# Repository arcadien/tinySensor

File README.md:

# TinySensor 

TinySensor aims to provide a customisable firmware and a hardware design for low-power environment sensors using wireless communication.

In the complete system, data is processed by a [Domoticz](https://domoticz.com/)/[RFlink](http://www.rflink.nl/blog2/) couple.
Data decoding is also tested using [RTL_433](https://github.com/merbanan/rtl_433) decoder.
Large part of the code, especially wireless encoders, are unit-tested.

## Supported MCUs
* ATTiny84a
* ATMega328p: started on branch `feat/328p_hal`, not merged

## Supported sensors
* I2C sensors (eg. [Bosch BME/BMP280](https://www.bosch-sensortec.com/bst/products/all_products/bme280))
* Analog sensors (eg. [LM35](http://www.ti.com/lit/ds/symlink/lm35.pdf))
* OneWire sensors (eg. [Dallas DS18S20](https://datasheets.maximintegrated.com/en/ds/DS18S20.pdf))
* Luminosity sensor ([ROHM BH1750](https://www.mouser.com/datasheet/2/348/bh1750fvi-e-186247.pdf), I2C)

## Wireless technology
* "one pin" emitters. Tested with low-cost 433 MHz emitters.

## Wireless protocols
* Environment frame (temperature, humidity, pressure): Oregon Scientific v3 **or** Lacrosse WS7000, at most one per build. A build without either sends no environment frame.
* Luminosity: always a dedicated Lacrosse WS7000 frame (Oregon has no light frame), so `LACROSSE_ID` is required whenever the BH1750 is fitted.
* Battery level and analog input: optional X10 RFXmeter frames, not sent when the battery is low.

## Used libraries
Various libraries are used here, and some where tweaked to remove any Arduino dependencies, making the whole firmware more compact:
* Sparkfun [BME280 sensor library](https://github.com/sparkfun/SparkFun_BME280_Arduino_Library) with all SPI related code removed
* [Tiny I2C](https://github.com/arcadien/tiny-i2c.git) of [David Johnson-Davies](https://github.com/technoblogy)
* [Unity test harness](http://www.throwtheswitch.org/unity) from Throw The Switch, for all testing code
* DS18B20 library of [Jacek Wieczorek](https://github.com/Jacajack/avr-ds18b20)

## Useful documentation about low power AVR
* [AVR4013: picoPower Basics](http://www.microchip.com/downloads/en/AppNotes/doc8349.pdf)

## Development

The firmware is built with [PlatformIO](https://platformio.org/) and configured entirely at build time: each physical sensor is one PlatformIO environment (`S_02`…`S_05`, `robot`, `devmodule`, `SOLAR_TEST`) whose `build_flags` select protocol, sensors and calibration. See [docs/environments.md](docs/environments.md) to calibrate or add a board.

```bash
pio test -e native_debug        # encoder and library unit tests, on the host
pio test -e native_cycle_oregon # one measurement cycle (runCycle) per build variant;
                                # also native_cycle_oregon_vcc, _lacrosse, _x10
pio run -e S_02                 # firmware for one board
pio run -e S_02 -t upload       # flash it
```

CI runs the native tests, compile-fail checks for invalid flag combinations (`test/compile_fail/`), sensor-variant checks (`test/build_variants/`), `clang-format` and a build of every board.

* Architecture: [docs/architecture.md](docs/architecture.md)
* Step debugging over debugWIRE: [docs/debugging.md](docs/debugging.md)
* Requirements: `requirements/*.md` (requirement-based development, see `CLAUDE.md`)

## Hardware and enclosure

* KiCad board (v3.0) in `hardware/tinysensor/`, with its [backlog](hardware/tinysensor/BACKLOG.md) and a [rework guide for v2.2 boards](hardware/tinysensor/REWORK_v2.2.md).
* OpenSCAD enclosures (wall box, radiation shield, mushroom) in `openscad/`, see [openscad/README.md](openscad/README.md).

## Hardware options

TinySensor can use combination of sensors, the limit comes from amount of flash memory on the ATTiny.

### DS18B20

OneWire sensor, cheap and efficient.

### BMP/BME 280 environment sensor
The [BMP280](https://www.bosch-sensortec.com/products/environmental-sensors/pressure-sensors/pressure-sensors-bmp280-1.html) and the [BME280](https://www.bosch-sensortec.com/products/environmental-sensors/humidity-sensors-bme280/) share the same library, but the BME provide humidity sensing, and thus use more memory.

### Analog sensor

Analog sensor can be used for [LM35](https://www.ti.com/lit/ds/symlink/lm35.pdf) temperature sensor, or [LDR](https://en.wikipedia.org/wiki/Photoresistor).

### LM35 temperature sensor

On v2.2 and v3.0 boards running from 2×AA/AAA, the LM35 can be powered by an off-board 5 V boost module switched on PB2 only during measurements (`USE_SWITCHED_5V`), see [VARIANTE_LM35.md](hardware/tinysensor/VARIANTE_LM35.md). The instructions below are for v2.1.

#### Without negative temperature support
A 0v ground reference is needed.
Solder pads *2* and *3* of **J4**, (rear side) as well **JP3**. 

#### With negative temperature support
In the case of a *-CAZ* version, temperature below 0 can be measured. 
To allow this, two 1N914 diodes must be placed to put the sensor reference below 0v. This setup is documented in the LM35 datasheet.
On TinySensor board v2.1 and up, this can be implemented by:
* solding **D2** and **D3** diodes
* solding **R4** with a value of 18k
* solding **JP3** to bypass C3 capacitor
* solding pads *1* and *2* of **J4** (rear side) to set ground reference.

#### Notes about swing

You can add a filter capacitor *C3* to avoid swing if the wire is long. In this case, do not solder *JP3*.
See datasheet for details.

### LDR
Use the right value for **R4** (should match the used LDR) and solder **JP3** and, on **JP4**, middle and *3* pads. This way, there will be no RC filter (no cap because of **J3**) and Vss analog reference thanks of **JP4**.

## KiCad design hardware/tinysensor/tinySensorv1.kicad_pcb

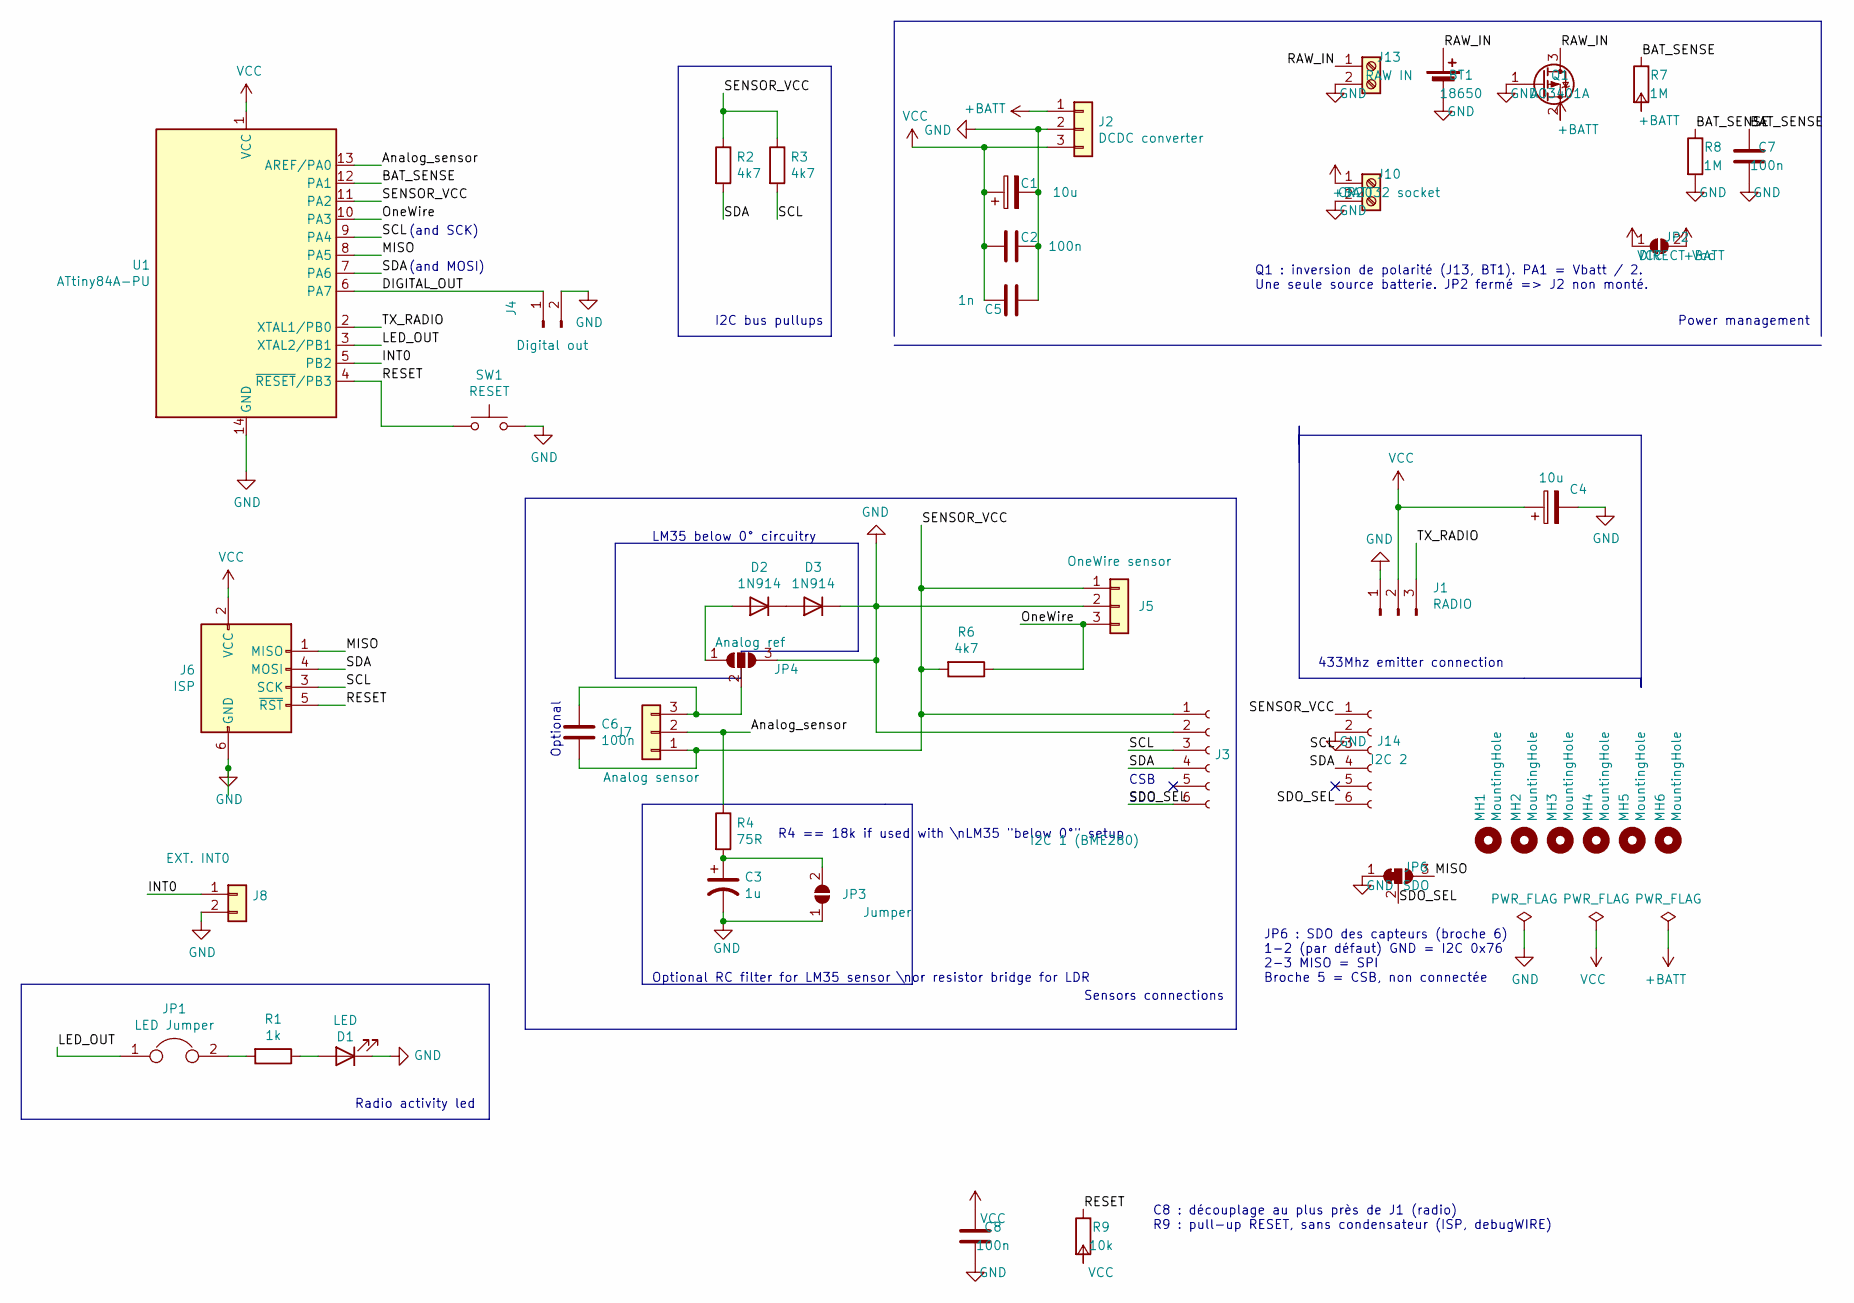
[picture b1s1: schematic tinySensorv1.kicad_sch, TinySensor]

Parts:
BT1: 18650; BatteryHolder_MPD_BH-18650-PC2
C1, C4: 10u; CP_Radial_D5.0mm_P2.50mm
C2: 100n; C_Rect_L7.0mm_W2.0mm_P5.00mm
C3: 1u; CP_Radial_D4.0mm_P1.50mm
C5: 1n; C_Disc_D3.0mm_W1.6mm_P2.50mm
C6, C7, C8: 100n; C_0805_2012Metric
D1: LED; LED_D1.8mm_W3.3mm_H2.4mm
D2, D3: 1N914; D_DO-35_SOD27_P7.62mm_Horizontal
J1: RADIO; PinHeader_1x03_P2.54mm_Vertical
J2: DCDC converter; DC-DC_0.9v-3.3v_to_3.3v
J3: I2C 1 (BME280); JST_EH_B6B-EH-A_1x06_P2.50mm_Vertical
J4: Digital out; PinHeader_1x02_P2.54mm_Vertical
J5: OneWire sensor; PinHeader_1x03_P2.54mm_Vertical
J6: ISP; ICSP_SOCKET_MINI_2x3
J7: Analog sensor; PinHeader_1x03_P2.54mm_Vertical
J8: EXT. INT0; PinHeader_1x02_P2.54mm_Vertical
J10: CR2032 socket; BatteryHolder_Keystone_106_1x21mm
J13: RAW IN; TerminalBlock_bornier-2_P5.08mm
J14: I2C 2; JST_EH_B6B-EH-A_1x06_P2.50mm_Vertical
JP1: LED Jumper; PinHeader_1x02_P2.54mm_Vertical
JP2: DIRECT Vcc; SolderJumper-2_P1.3mm_Open_TrianglePad1.0x1.5mm
JP3: Jumper; SolderJumper-2_P1.3mm_Open_TrianglePad1.0x1.5mm
JP4: Analog ref; SolderJumper-3_P1.3mm_Open_Pad1.0x1.5mm_NumberLabels
JP6: SDO; SolderJumper-3_P1.3mm_Bridged12_RoundedPad1.0x1.5mm
MH1, MH2, MH3, MH4, MH5, MH6: MountingHole; MountingHole_2.7mm_M2.5
Q1: AO3401A; SOT-23
R1: 1k; R_Axial_DIN0204_L3.6mm_D1.6mm_P7.62mm_Horizontal
R2, R3, R6: 4k7; R_Axial_DIN0204_L3.6mm_D1.6mm_P7.62mm_Horizontal
R4: 75R; R_Axial_DIN0204_L3.6mm_D1.6mm_P7.62mm_Horizontal
R7, R8: 1M; R_0805_2012Metric
R9: 10k; R_0805_2012Metric
SW1: RESET; SW_PUSH_6mm_H4.3mm
U1: ATtiny84A-PU; DIP-14_W7.62mm

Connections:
+BATT: J2.1, J10.1, JP2.2 (B), Q1.2 (S), R7.2
/Analog_sensor: J7.2, R4.1, U1.13 (AREF/PA0)
/BAT_SENSE: C7.1, R7.1, R8.1, U1.12 (PA1)
/DIGITAL_OUT: J4.1, U1.6 (PA7)
/INT0: J8.1, U1.5 (PB2)
/LED_OUT: JP1.1, U1.3 (XTAL2/PB1)
/MISO: J6.1 (MISO), JP6.3 (B), U1.8 (PA5)
/OneWire: J5.3, R6.1, U1.10 (PA3)
/RAW_IN: BT1.1 (+), J13.1, Q1.3 (D)
/RESET: J6.5 (~RST), R9.1, SW1.1, U1.4 (~RESET/PB3)
/SCL: J3.3, J6.3 (SCK), J14.3, R3.2, U1.9 (PA4)
/SDA: J3.4, J6.4 (MOSI), J14.4, R2.2, U1.7 (PA6)
/SDO_SEL: J3.6, J14.6, JP6.2 (C)
/SENSOR_VCC: C6.1, J3.1, J5.1, J7.1, J14.1, R2.1, R3.1, R6.2, U1.11 (PA2)
/TX_RADIO: J1.3, U1.2 (XTAL1/PB0)
GND: BT1.2 (-), C1.2, C2.1, C3.2, C4.2, C5.2, C7.2, C8.2, D1.1 (K), D3.1 (K), J1.1, J2.2, J3.2, J4.2, J5.2, J6.6 (GND), J8.2, J10.2, J13.2, J14.2, JP3.1 (A), JP4.3 (B), JP6.1 (A), Q1.1 (G), R8.2, SW1.2, U1.14 (GND)
unnamed: D1.2 (A), R1.1
unnamed: D2.2 (A), JP4.1 (A)
unnamed: D2.1 (K), D3.2 (A)
unnamed: C6.2, J7.3, JP4.2 (C)
unnamed: JP1.2, R1.2
unnamed: C3.1, JP3.2 (B), R4.2
VCC: C1.1, C2.2, C4.1, C5.1, C8.1, J1.2, J2.3, J6.2 (VCC), JP2.1 (A), R9.2, U1.1 (VCC)

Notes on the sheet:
CSB
Radio activity led
Power management
Optional RC filter for LM35 sensor \nor resistor bridge for LDR
(and SCK)
SDO
Sensors connections
LM35 below 0° circuitry
I2C bus pullups
(and MOSI)
Optional
R4 == 18k if used with \nLM35 "below 0°" setup
433Mhz emitter connection
Q1 : inversion de polarité (J13, BT1). PA1 = Vbatt / 2. Une seule source batterie. JP2 fermé => J2 non monté.
JP6 : SDO des capteurs (broche 6) 1-2 (par défaut) GND = I2C 0x76 2-3 MISO = SPI Broche 5 = CSB, non connectée
C8 : découplage au plus près de J1 (radio) R9 : pull-up RESET, sans condensateur (ISP, debugWIRE)

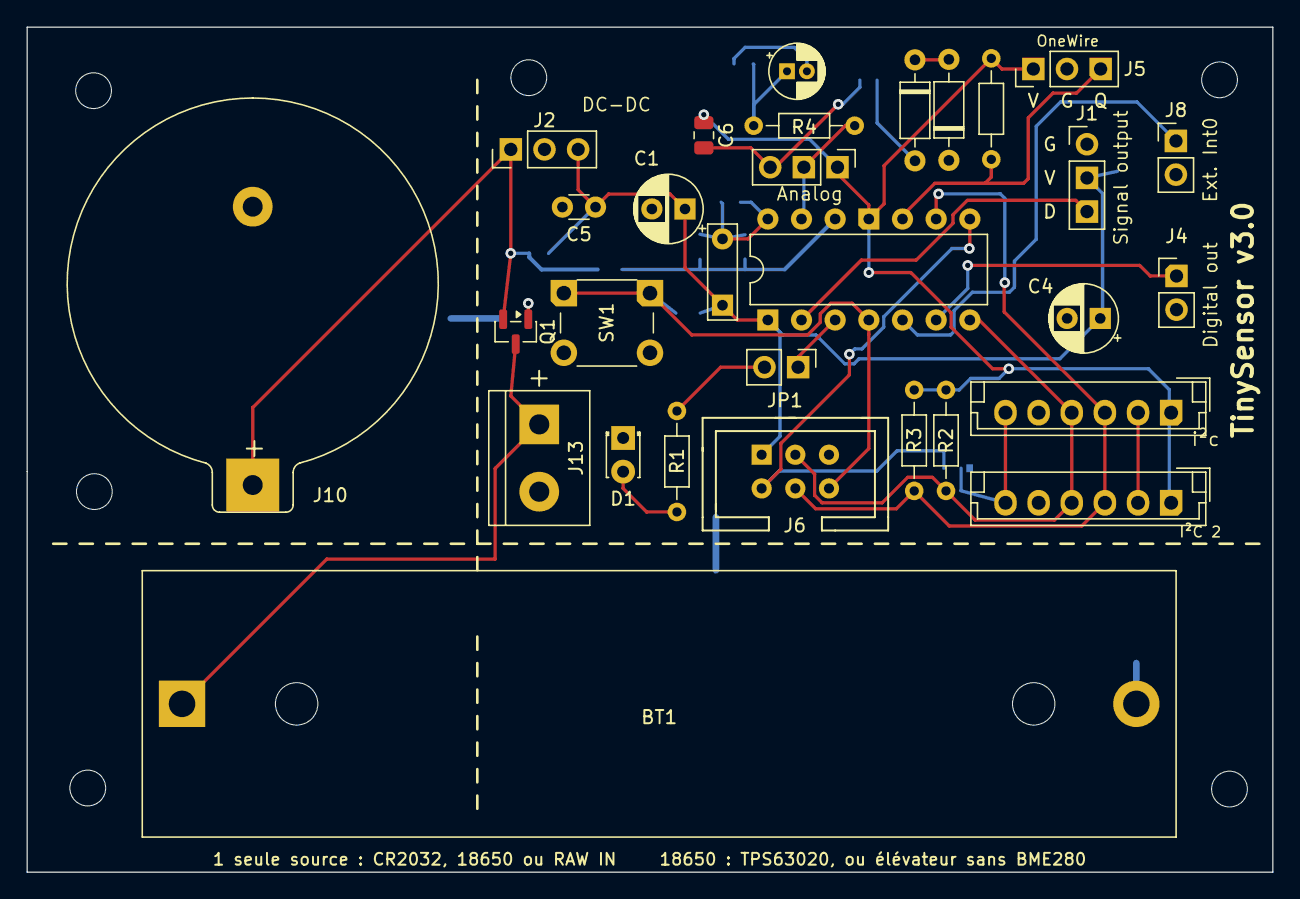
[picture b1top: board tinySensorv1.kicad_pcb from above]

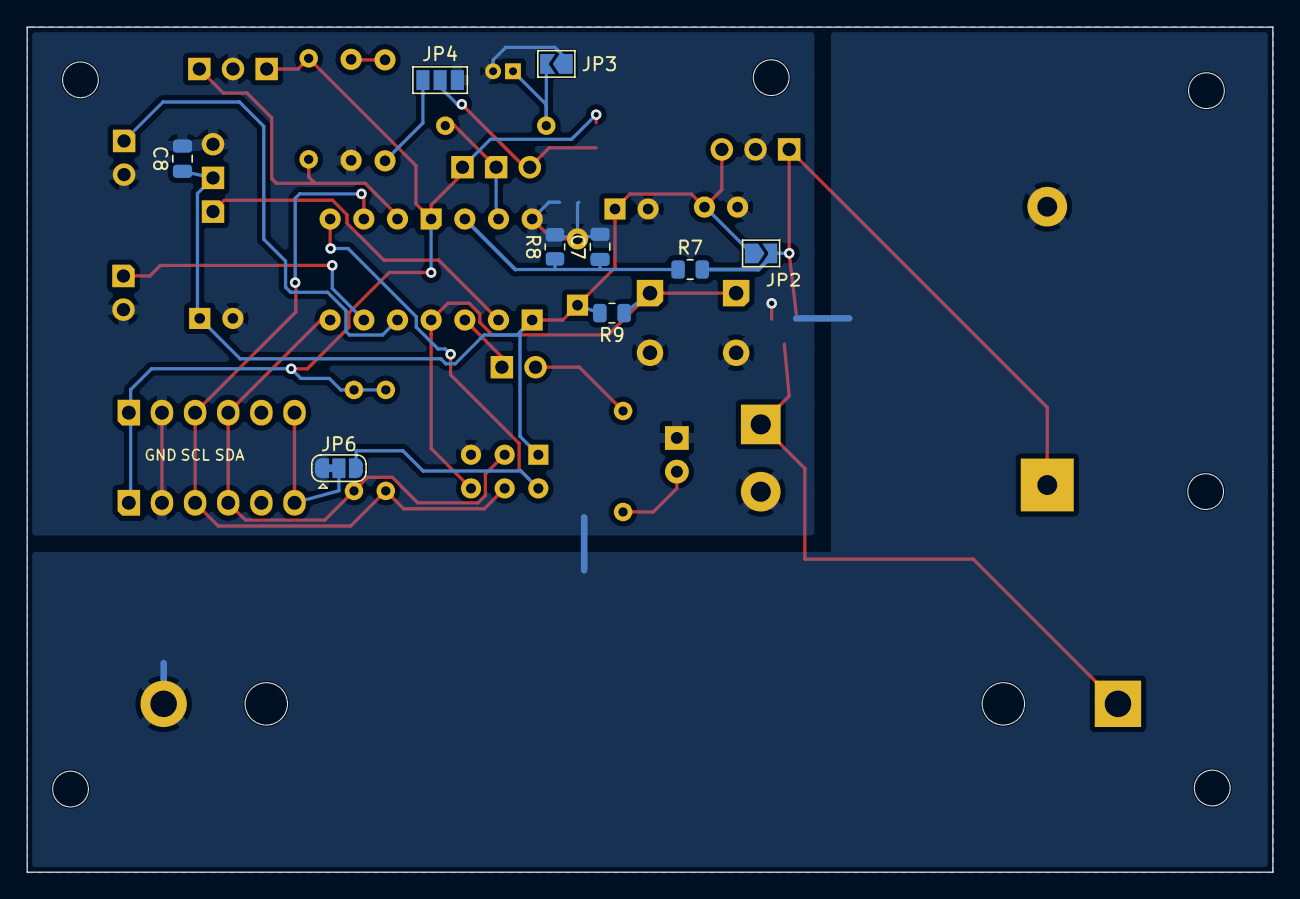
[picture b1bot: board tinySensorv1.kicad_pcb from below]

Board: 2 copper layers, 94.0 x 63.8 mm, 45 parts (9 on the bottom side), 23 nets.

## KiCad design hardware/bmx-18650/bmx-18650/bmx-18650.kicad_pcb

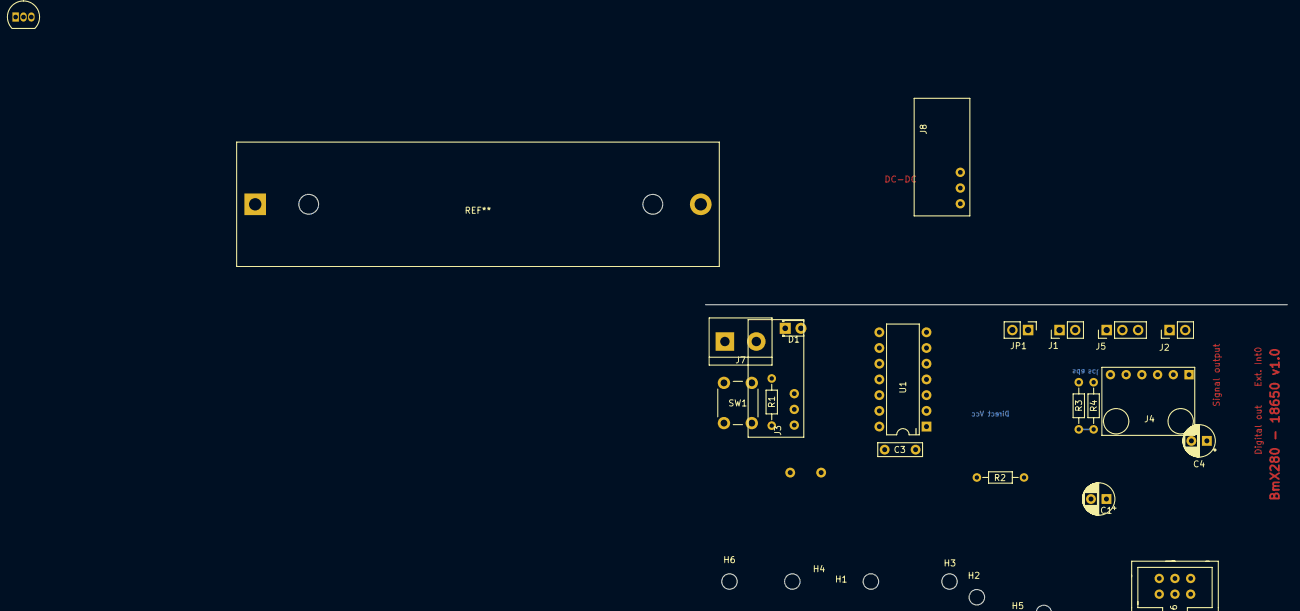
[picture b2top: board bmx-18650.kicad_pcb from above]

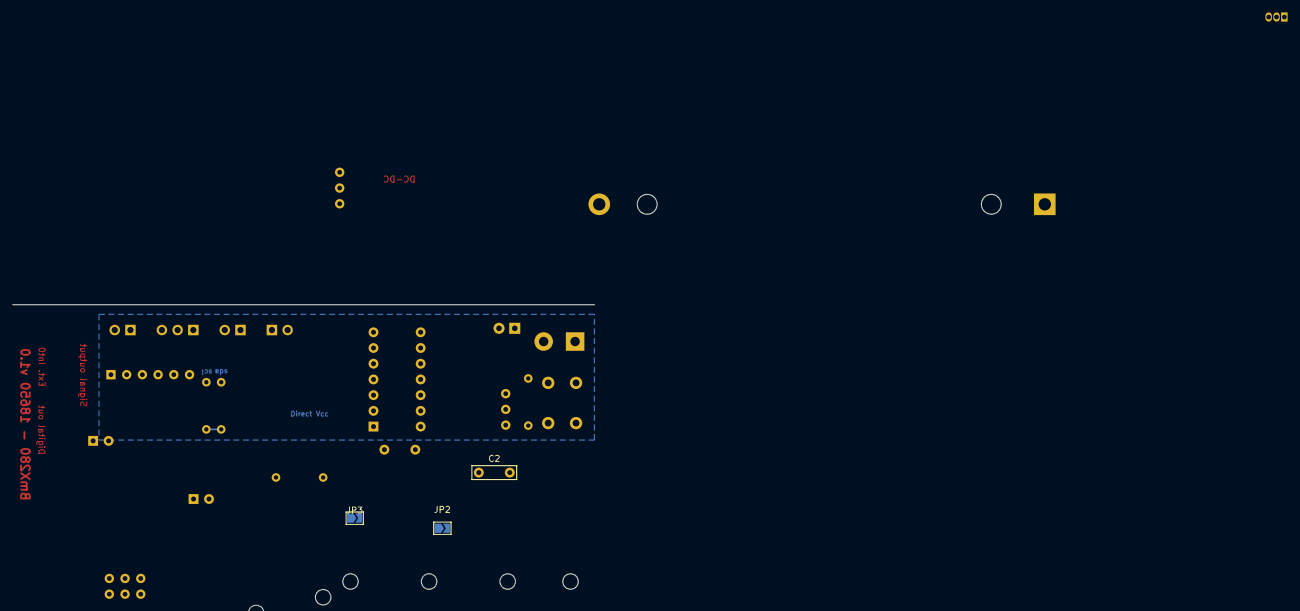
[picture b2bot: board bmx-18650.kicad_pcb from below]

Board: 2 copper layers, 29 parts (3 on the bottom side), 17 nets.

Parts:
C1, C4: 10u; CP_Radial_D5.0mm_P2.50mm
C2, C3: 100n; C_Rect_L7.0mm_W2.0mm_P5.00mm
D1: LED; LED_D1.8mm_W3.3mm_H2.4mm
H1, H2, H3, H4, H5, H6: MountingHole; MountingHole_2.5mm
J1: Ext. interrupt; PinHeader_1x02_P2.54mm_Vertical
J2: Digital out; PinHeader_1x02_P2.54mm_Vertical
J3: VCC charge pump; DC-DC_0.9v-3.3v_to_3.3v
J4: BMx280 socket; BMx280_breakout
J5: Radio emitter; PinHeader_1x03_P2.54mm_Vertical
J6: ISP; ICSP_SOCKET_MINI_2x3
J7: Terminal; TerminalBlock_bornier-2_P5.08mm
J8: RF charge pump; DC-DC_0.9v-3.3v_to_3.3v
JP1: LED Jumper; PinHeader_1x02_P2.54mm_Vertical
JP2, JP3: Bypass; SolderJumper-2_P1.3mm_Open_TrianglePad1.0x1.5mm
Q1: BS170; TO-92_Inline
R1, R3, R4: R; R_Axial_DIN0204_L3.6mm_D1.6mm_P7.62mm_Horizontal
R2: 10k; R_Axial_DIN0204_L3.6mm_D1.6mm_P7.62mm_Horizontal
SW1: SW_Push; SW_PUSH_6mm_H4.3mm
U1: ATtiny84A-PU; DIP-14_W7.62mm

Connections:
+BATT: J3.1, J7.1, J8.3, JP2.2 (B), JP3.1 (A), U1.12 (PA1)
/DIGITAL_OUT: J2.1, U1.6 (PA7)
/INT0: J1.1, U1.5 (PB2)
/LED_OUT: JP1.1, U1.3 (XTAL2/PB1)
/MISO: J6.1 (MISO), U1.8 (PA5)
/RESET: J6.5 (~RST), R2.1, SW1.1, U1.4 (~RESET/PB3)
/SCL: J4.3, J6.3 (SCK), R4.2, U1.9 (PA4)
/SDA: J4.4, J6.4 (MOSI), R3.2, U1.7 (PA6)
/SENSOR_VCC: J4.1, Q1.2 (G), R3.1, R4.1, U1.11 (PA2)
/TX_RADIO: J5.3, U1.2 (XTAL1/PB0)
GND: C1.2, C2.2, C3.1, C4.2, D1.2 (A), J1.2, J2.2, J3.2, J4.2, J4.6, J5.1, J6.6 (GND), J7.2, Q1.3 (S), SW1.2, U1.14 (GND)
unnamed: D1.1 (K), R1.1
unnamed: J8.2, Q1.1 (D)
unnamed: JP1.2, R1.2
unnamed: C2.1, U1.13 (AREF/PA0)
VCC: C1.1, C3.2, J3.3, J6.2 (VCC), JP2.1 (A), R2.2, U1.1 (VCC)
VDD: C4.1, J5.2, J8.1, JP3.2 (B)

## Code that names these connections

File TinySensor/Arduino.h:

/*
  pins_arduino.h - Pin definition functions for Arduino
  Part of Arduino - http://www.arduino.cc/

  Copyright (c) 2007 David A. Mellis
  Copyright (c) 2015~2020 Spence Konde

  This library is free software; you can redistribute it and/or
  modify it under the terms of the GNU Lesser General Public
  License as published by the Free Software Foundation; either
  version 2.1 of the License, or (at your option) any later version.

  This library is distributed in the hope that it will be useful,
  but WITHOUT ANY WARRANTY; without even the implied warranty of
  MERCHANTABILITY or FITNESS FOR A PARTICULAR PURPOSE.  See the GNU
  Lesser General Public License for more details.

  You should have received a copy of the GNU Lesser General
  Public License along with this library; if not, write to the
  Free Software Foundation, Inc., 59 Temple Place, Suite 330,
  Boston, MA  02111-1307  USA

  $Id: wiring.h 249 2007-02-03 16:52:51Z mellis $
*/

#ifndef Pins_Arduino_h
#define Pins_Arduino_h

#define ATTINYX4 1
#define __AVR_ATtinyX4__
#define USE_SOFTWARE_SPI 1

#include <avr/pgmspace.h>

#define NUM_DIGITAL_PINS            12
#define NUM_ANALOG_INPUTS           8

#define analogInputToDigitalPin(p)  (p)

#define digitalPinHasPWM(p)         ((p) == 5 || (p) == 6 || (p) == 7 || (p) == 8)

//This part has a USI, not an SPI module. Accordingly, there is no MISO/MOSI in hardware. There's a DI and a DO. When the chip is used as master, DI is used as MISO, DO is MOSI; the defines here specify the pins for master mode, as SPI master is much more commonly used in Arduino-land than SPI slave, and these defines are required for compatibility. Be aware of this when using the USI SPI fucntionality (and also, be aware that the MISO and MOSI markings on the pinout diagram in the datasheet are for ISP programming, where the chip is a slave. The pinout diagram included with this core attempts to clarify this)

#define ADC_TEMPERATURE 34

#define SS   3
#define MOSI 5
#define MISO 6
#define SCK  4


#define USI_DDR_PORT DDRA
#define USI_SCK_PORT DDRA
#define USCK_DD_PIN DDA4
#define DO_DD_PIN DDA5
#define DI_DD_PIN DDA6
#  define DDR_USI DDRA
#  define PORT_USI PORTA
#  define PIN_USI PINA
#  define PORT_USI_SDA PORTA6
#  define PORT_USI_SCL PORTA4
#  define PIN_USI_SDA PINA6
#  define PIN_USI_SCL PINA4
#  define USI_START_VECTOR USI_START_vect
#  define USI_OVERFLOW_VECTOR USI_OVF_vect
#  define DDR_USI_CL DDR_USI
#  define PORT_USI_CL PORT_USI
#  define PIN_USI_CL PIN_USI
#ifndef USI_START_COND_INT
#  define USI_START_COND_INT USISIF
#endif

static const uint8_t SDA = 6;
static const uint8_t SCL = 4;

//Ax constants should not be used for digitalRead/digitalWrite/analogWrite functions, only analogRead().
//#define ANALOG_PINS_ARE_ADC_NUMBERS 1
static const uint8_t A0 = 0x80 | 0;
static const uint8_t A1 = 0x80 | 1;
static const uint8_t A2 = 0x80 | 2;
static const uint8_t A3 = 0x80 | 3;
static const uint8_t A4 = 0x80 | 4;
static const uint8_t A5 = 0x80 | 5;
static const uint8_t A6 = 0x80 | 6;
static const uint8_t A7 = 0x80 | 7;

#define PIN_PA0  (0)
#define PIN_PA1  ( 1)
#define PIN_PA2  ( 2)
#define PIN_PA3  ( 3)
#define PIN_PA4  ( 4)
#define PIN_PA5  ( 5)
#define PIN_PA6  ( 6)
#define PIN_PA7  ( 7)
#define PIN_PB0  ( 10)
#define PIN_PB1  ( 9)
#define PIN_PB2  ( 8)
#define PIN_PB3  (11)  /* RESET */
#define LED_BUILTIN (8)

//Legacy
#define PIN_A0  (0)
#define PIN_A1  ( 1)
#define PIN_A2  ( 2)
#define PIN_A3  ( 3)
#define PIN_A4  ( 4)
#define PIN_A5  ( 5)
#define PIN_A6  ( 6)
#define PIN_A7  ( 7)
#define PIN_B0  ( 10)
#define PIN_B1  ( 9)
#define PIN_B2  ( 8)
#define PIN_B3  (11)  /* RESET */
#define LED_BUILTIN (8)

#define PINMAPPING_CW

//----------------------------------------------------------
//----------------------------------------------------------
//Core Configuration (used to be in core_build_options.h)



//Choosing not to initialise saves power and flash. 1 = initialise.
#define INITIALIZE_ANALOG_TO_DIGITAL_CONVERTER    1
#define INITIALIZE_SECONDARY_TIMERS               1
/*
  The old standby ... millis on Timer 0.
*/
#define TIMER_TO_USE_FOR_MILLIS                   0

/*
  Where to put the software serial? (Arduino Digital pin numbers)
*/
//WARNING, if using software, TX is on AIN0, RX is on AIN1. Comparator is favoured to use its interrupt for the RX pin.
#define USE_SOFTWARE_SERIAL           1
//Please define the port on which the analog comparator is found.
#define ANALOG_COMP_DDR               DDRA
#define ANALOG_COMP_PORT              PORTA
#define ANALOG_COMP_PIN               PINA
#define ANALOG_COMP_AIN0_BIT          1
#define ANALOG_COMP_AIN1_BIT          2


/*
  Analog reference bit masks.
*/
// VCC used as analog reference, disconnected from PA0 (AREF)
#define DEFAULT (0)
// External voltage reference at PA0 (AREF) pin, internal reference turned off
#define EXTERNAL (1)
// Internal 1.1V voltage reference
#define INTERNAL (2)
#define INTERNAL1V1 INTERNAL

//----------------------------------------------------------
//----------------------------------------------------------
//----------------------------------------------------------
//----------------------------------------------------------


// PCICR = Pin Change Interrupt Control Register
#define digitalPinToPCICR(p)    (((p) >= 0 && (p) <= 11) ? (&GIMSK) : ((uint8_t *)NULL))
#define digitalPinToPCICRbit(p) ( ((p) <= 7) ? PCIE0 : PCIE1 )
#define digitalPinToPCMSK(p)    ( ((p) <= 7) ? (&PCMSK0) : (((p) <= 10) ? (&PCMSK1) : ((uint8_t *)NULL)) )
#define digitalPinToPCMSKbit(p) ( ((p) <= 7) ? (p) : (10 - (p)) )

#define digitalPinToInterrupt(p)  ((p) == 8 ? 0 : NOT_AN_INTERRUPT)
#ifdef ARDUINO_MAIN
#warning "This is the CLOCKWISE pin mapping - make sure you're using the pinout diagram with the pins in clockwise order"
// ATMEL ATTINY84 / ARDUINO
//
//                           +-\/-+
//                     VCC  1|    |14  GND
//            (D  10)  PB0  2|    |13  PA0  (D  0)        AREF
//             (D  9)  PB1  3|    |12  PA1  (D  1)
//             (D 11)  PB3  4|    |11  PA2  (D  2)
//  PWM  INT0  (D  8)  PB2  5|    |10  PA3  (D  3)
//  PWM        (D  7)  PA7  6|    |9   PA4  (D  4)
//  PWM        (D  6)  PA6  7|    |8   PA5  (D  5)        PWM
//                           +----+
const uint16_t PROGMEM port_to_mode_PGM[] =
{
  NOT_A_PORT,
  (uint16_t)&DDRA,
  (uint16_t)&DDRB,
};

const uint16_t PROGMEM port_to_output_PGM[] =
{
  NOT_A_PORT,
  (uint16_t)&PORTA,
  (uint16_t)&PORTB,
};

const uint16_t PROGMEM port_to_input_PGM[] =
{
  NOT_A_PORT,
  (uint16_t)&PINA,
  (uint16_t)&PINB,
};

const uint8_t PROGMEM digital_pin_to_port_PGM[] =
{
  PA, /* 0 */
  PA,
  PA,
  PA,
  PA,
  PA,
  PA,
  PA,
  PB, /* 8 */
  PB,
  PB,
  PB, /* 11 */
};



const uint8_t PROGMEM digital_pin_to_bit_mask_PGM[] =
{
  _BV(0), /* port A */
  _BV(1),
  _BV(2),
  _BV(3),
  _BV(4),
  _BV(5),
  _BV(6),
  _BV(7),
  _BV(2), /* port B */
  _BV(1),
  _BV(0),
  _BV(3),
};

const uint8_t PROGMEM digital_pin_to_timer_PGM[] =
{
  NOT_ON_TIMER,
  NOT_ON_TIMER,
  NOT_ON_TIMER,
  NOT_ON_TIMER,
  NOT_ON_TIMER,
  TIMER1B, /* OC1B */
  TIMER1A, /* OC1A */
  TIMER0B, /* OC0B */
  TIMER0A, /* OC0A */
  NOT_ON_TIMER,
  NOT_ON_TIMER,
  NOT_ON_TIMER,
};

#endif

#endif




//Old code, just here for temporary backup until I decide it is not needed.
/*
//WARNING, if using software, RX must be on a pin which has a Pin change interrupt <= 7 (e.g. PCINT6, or PCINT1, but not PCINT8)
#define USE_SOFTWARE_SERIAL             1
//These are set to match Optiboot pins.
#define SOFTWARE_SERIAL_PORT            PORTA
#define SOFTWARE_SERIAL_TX              9
#define SOFTWARE_SERIAL_PIN             PINA
#define SOFTWARE_SERIAL_RX              8*/

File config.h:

/*
 * config.h
 *
 * Created: 19/11/2018 22:14:40
 *  Author: aurelien
 */

#ifndef CONFIG_H_
#define CONFIG_H_

#include <inttypes.h>

// sleep 32s between each sample and
// emission
#define SLEEP_TIME_IN_SECONDS (8 * 4)

/*
 * 1-wire interface is on PA3
 * Power for radio is on PA2 (sensor_vcc)
 * LED pin is PB1
 * PWM pin is PA7
 * SDA pin is PA6
 * SCL pin is PA4
 * MISO pin is PA5
 * TX radio pin is PB0
 * BAT sensor pin is PA1
 * analog sensor pin is PA0
 */
#define LED_PIN PB1
#define PWM_PIN PA7
#define TX_RADIO_PIN PB0
#define RADIO_POWER_PIN PA2
#define BAT_SENSOR_PIN PA1

// Sensors
#define USE_BMP280
//#define USE_BME280
//#define USE_DS18B20 
// Protocols
#define USE_OREGON 1

// 0x5A, 0x5D pressure, temp, hygro
// 0xEA, 0x4C temp only
const uint8_t OREGON_TYPE[] = {0xEA, 0x4C};
const uint8_t OREGON_ID = 0xCB;

/*
 * MODE_0 0 // Temperature only [THN132N]
 * MODE_1 1 // Temperature + Humidity [THGR2228N]
 * MODE_2 2 // Temperature + Humidity + Baro() [BTHR918N]
 */
#define OREGON_MODE MODE_0

#endif /* CONFIG_H_ */
